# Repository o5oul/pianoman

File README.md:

# pianoman 
MIDI Keyboard, uses mechanical switches to detect inputs. Has a built in rotary encoder knob to act as a volume control.

<break>

## **Notes:**
- PCB can be purchased from JLPCB or PCBway, all parts will be listed + sample purchase links will be given.
- Switches should be PCB mounted, as there is no plate to hold the switches in place.

## **Build instructions:**
- Begin by inserting five (5) M2 screws into the base, then connecting them to the M2 standoffs through the other end.
- Solder the Seeed Studio XIAO ESP32 onto the given space.
- Solder the switches and rotary encoder onto the PCB.
- Once the soldering is completed, connect the PCB to a PC and write on the firmware.

## **Parts List: (For South-East Asia)**
- [12 x Huano Sakura v2 switches](https://www.aliexpress.com/item/1005008819780366.html?spm=a2g0o.productlist.main.2.b9a55dfaYEBNLf&algo_pvid=fca31fea-e6e8-41a6-a7f7-b9bd1384eb48&algo_exp_id=fca31fea-e6e8-41a6-a7f7-b9bd1384eb48-1&pdp_ext_f=%7B%22order%22%3A%22239%22%2C%22eval%22%3A%221%22%2C%22fromPage%22%3A%22search%22%7D&pdp_npi=6%40dis%21MYR%2122.04%215.22%21%21%215.24%211.24%21%402101364a17903370173813828e0e0b%2112000046806379242%21sea%21MY%210%21ABX%211%210%21n_tag%3A-29910%3Bd%3Ad5cef2be%3Bm03_new_user%3A-29895%3BpisId%3A5000000216900886&curPageLogUid=wXyMIQGKpfFU&utparam-url=scene%3Asearch%7Cquery_from%3A%7Cx_object_id%3A1005008819780366%7C_p_origin_prod%3A)
- [SEEED XIAO ESP32-C3](https://shopee.com.my/Original-authentic-Seeed-Studio-XIAO-ESP32C3-xiahttps://shopee.com.my/-Luminense-PCB-Standoff-Brass-Standoff-M2-M3-120-pcs-300-pcs-set-i.63040732.15203389154?xptdk=49b2e936-5e74-4f0d-bcfd-47e3fcb39e03o-esp32-c3-thumb-WIFI-development-board-i.542060608.25985797324?extraParams=%7B%22display_model_id%22%3A223198452291%2C%22model_selection_logic%22%3A3%7D)
- [M2 Brass Standoffs](https://shopee.com.my/-Luminense-PCB-Standoff-Brass-Standoff-M2-M3-120-pcs-300-pcs-set-i.63040732.15203389154?xptdk=c7b95211-1365-4004-b025-c1b6e75623bb)

## **Recommended PCB Settings (JLCPCB):**
[JLCPCB Website](jlcpcb.com)
- Base Material: FR-4
- Layers: 2
- Product Type: Industrial/Consumer Electronics
- Deburring/Edge rounding: Yes
- Different Design: 1
- Delivery Format: Single PCB
- PCB Thickness: 1.6mm
- PCB Color: Black (Can be changed based on preference)
- Silkscreen: White
- Material Type: FR4 TG135
- Surface Finish: HASL (with lead)

## **Advanced:**

- Outer Copper Weight: 1oz
- Via Covering: Tented
- Via Plating Method: Not Specified
- Min via hole size/diameter: 0.3mm(0.4/0.45mm)
- Board Outline Tolerance: +-0.2mm(regular)
- Mark on PCB: Remove
- Gold Fingers: No

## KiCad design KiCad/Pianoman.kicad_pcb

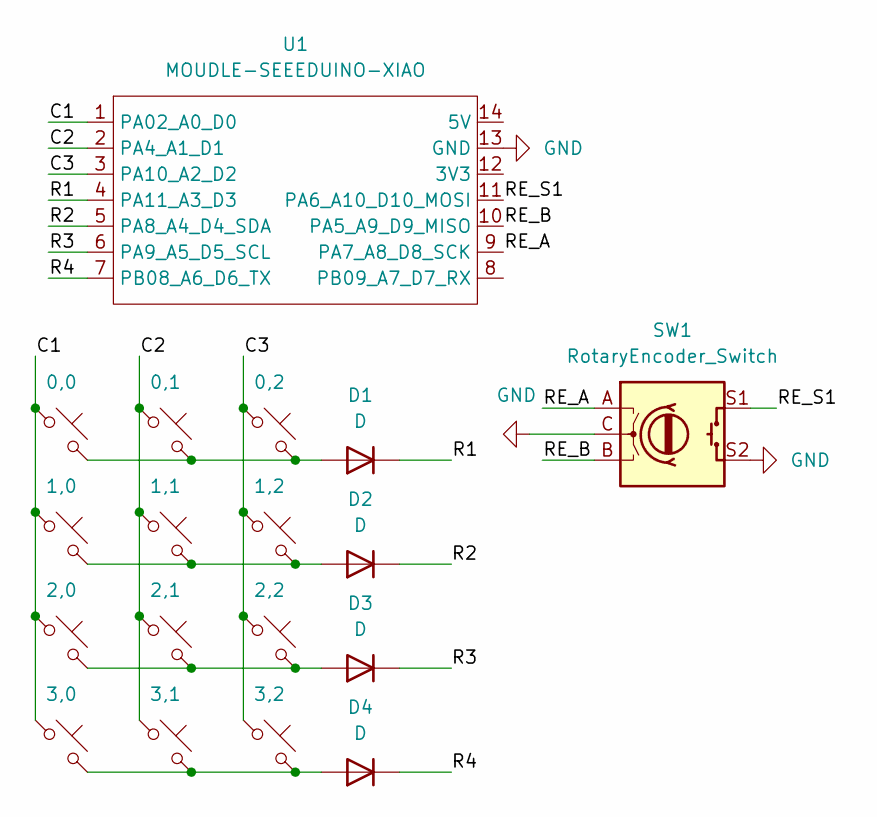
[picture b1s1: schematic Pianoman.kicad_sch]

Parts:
0,0, 0,1, 0,2, 1,0, 1,1, 1,2, 2,0, 2,1, 2,2, 3,0, 3,1, 3,2: SW_Push_45deg; SW_Cherry_MX_1.00u_PCB
D1, D2, D3, D4: D; D_SOD-123
SW1: RotaryEncoder_Switch; RotaryEncoder_Alps_EC11E-Switch_Vertical_H20mm
U1: MOUDLE-SEEEDUINO-XIAO; XIAO-Generic-Hybrid-14P-2.54-21X17.8MM

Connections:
/C1: 0,0.1, 1,0.1, 2,0.1, 3,0.1, U1.1 (PA02_A0_D0)
/C2: 0,1.1, 1,1.1, 2,1.1, 3,1.1, U1.2 (PA4_A1_D1)
/C3: 0,2.1, 1,2.1, 2,2.1, 3,2.1, U1.3 (PA10_A2_D2)
/R1: D1.1 (K), U1.4 (PA11_A3_D3)
/R2: D2.1 (K), U1.5 (PA8_A4_D4_SDA)
/R3: D3.1 (K), U1.6 (PA9_A5_D5_SCL)
/R4: D4.1 (K), U1.7 (PB08_A6_D6_TX)
/RE_A: SW1.A, U1.9 (PA7_A8_D8_SCK)
/RE_B: SW1.B, U1.10 (PA5_A9_D9_MISO)
/RE_S1: SW1.S1, U1.11 (PA6_A10_D10_MOSI)
GND: SW1.C, SW1.S2, U1.13 (GND)
unnamed: 0,0.2, 0,1.2, 0,2.2, D1.2 (A)
unnamed: 1,0.2, 1,1.2, 1,2.2, D2.2 (A)
unnamed: 2,0.2, 2,1.2, 2,2.2, D3.2 (A)
unnamed: 3,0.2, 3,1.2, 3,2.2, D4.2 (A)

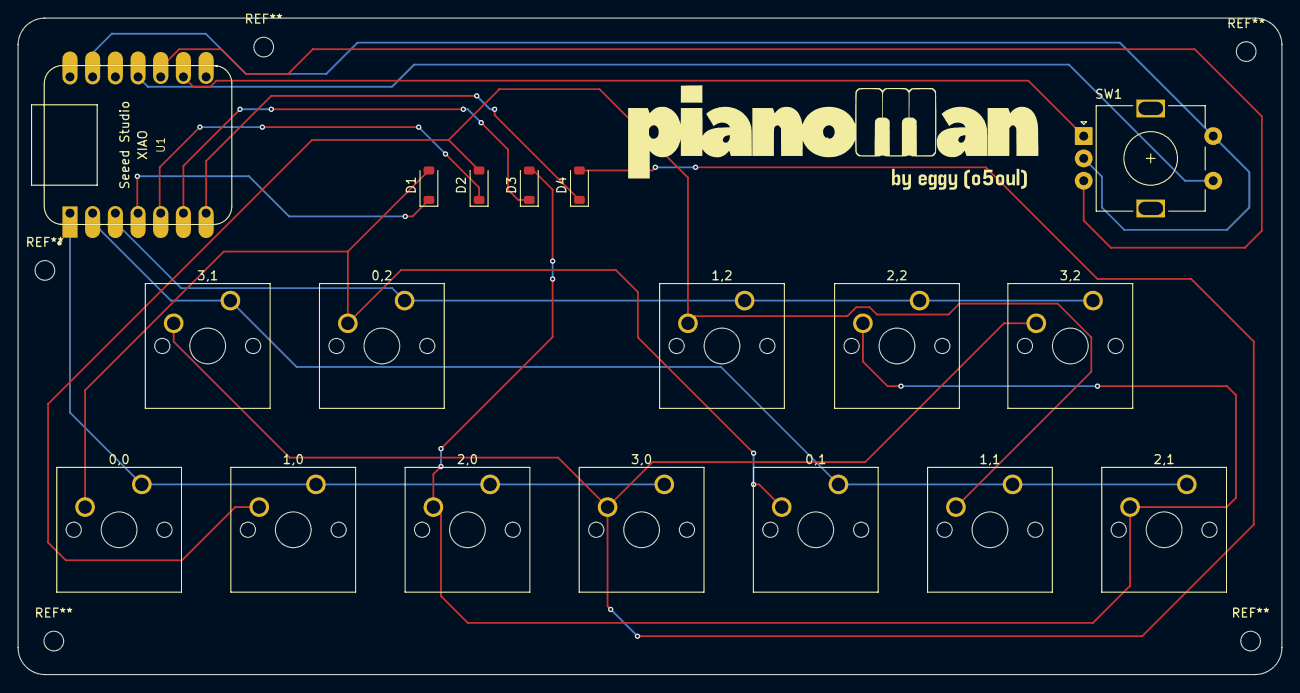
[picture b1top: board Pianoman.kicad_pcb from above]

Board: 2 copper layers, 141.5 x 73.5 mm, 18 parts (0 on the bottom side), 15 nets.
